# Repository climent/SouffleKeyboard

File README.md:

# Soufflé Keyboard

The Soufflé Keyboard is 6×4+1+4+1 keys column-staggered split keyboard with encoder support, based on the [Sofle](https://github.com/josefadamcik/SofleKeyboard) and re-inspired by the [Lily58](https://github.com/kata0510/Lily58) keyboards. It also takes a bit of layout ideas from the Kyria and the Ferris Sweep.

Soufflé was created by [Jesus Climent](https://https://github.com/climent/).

Key features:

*   Originally based on the Sofle V1 release layout,
    *   the two pinky columns have been lowered in the Soufflé: ~5mm for the V2, ~10mm for the V3 Sweep
    *   the thumb cluster has been repositioned to allow for equal reach of the keys
    *   a palm key has been added at the bottom of the outer pinkie column
*   Choice between rotary encoder or key switch for the inner keys.
*   Redone track layout with simplified, curved tracks.
*   V3 adds support for nice!nano with solder points for a battery and a power switch. 
*   Removed i2c communication betweek halves.

The VR release is a result of me experimenting with the RGB layout. However, I could not adapt to the displaced thumb cluster, so I returned to the V1 layout when I designed the V2.

## Images of keyboard

## Build notes

Build guide will be added soon. Meanwhile, the [Sofle Build Guide](https://josefadamcik.github.io/SofleKeyboard/build_guide.html) should be a good starting point.

## BOM

| Item                                                       | Quantity | Notes                                                                                                                                                                                                                                                |
|------------------------------------------------------------|----------|------------------------------------------------------------------------------------------------------------------------------------------------------------------------------------------------------------------------------------------------------|
| Soufflé PCB                                                | 2        |                                                                                                                                                                                                                                                      |
| Soufflé Plates                                             | 2+2      | Gerber files are provided to be ordered made of FR4. Can be 3D printed, extruding the upper plate at 1.5mm, the lower at a minimum of 1.5mm.                                                                                                         |
| Pro Micro pin MCU, or equivalent.                          | 2        | RP2040 recomended. Alternatives: Pro Micro (or clone), Elite-C, Elite-Pi, Frood, Liatris, nice!nano (for BT wireless)                                                                                                                                |
| 1N4148W Diodes                                             | 60       |                                                                                                                                                                                                                                                      |
| Kailh MX hotswap switch sockets                            | 60       |                                                                                                                                                                                                                                                      |
| MX switches                                                | 60       |                                                                                                                                                                                                                                                      |
| 1u keycaps                                                 | 60       |                                                                                                                                                                                                                                                      |
| M2, 7 mm brass (or other material) spacers                 | 10       | These are the optimal spacers. Longer ones work, too, but with 7mm the gap is minimal.                                                                                                                                                               |
| M2x0.4mm, 5mm length flat head screws                      | 20       |                                                                                                                                                                                                                                                      |
| M2x0.4mm, 7mm length flat head screws                      | 4        | If using OLED screen plexiglass protectors.                                                                                                                                                                                                          |
| PJ-320A TRRS 3.5mm Audio Jack Connector Through Holes      | 2        | Not necessary if you are using wireless, via nice!nano.                                                                                                                                                                                              |
| Surface Momentary Tact Switch, 3mm x 4mm x 4.3mm           | 2        |                                                                                                                                                                                                                                                      |
| 2.54mm Round Hole Male Tin Gold Female Pin Headers, 40p    | 2 (opt)  | HIGHLY RECOMMENDED. However, If you want to solder the MCU directly to the board, these are not necessary.                                                                                                                                           |
| Mill Max socket pins                                       | 48 (opt) | Add 8 extra for the OLED screen, if used. Alternatively, socketing can also be done with diode legs.                                                                                                                                                 |
| 1.25u keycaps                                              | 2 (opt)  | Alternative to 2x 1u keycaps.                                                                                                                                                                                                                        |
| SSD1306 128x64 OLED                                        | 2 (opt)  |                                                                                                                                                                                                                                                      |
| EC11 Encoder                                               | 2 (opt)  | Optional, as the board allows for either 2x encoders or switches.                                                                                                                                                                                    |
| Encoder knob, 16mm                                         | 2 (opt)  | If encoders are used.                                                                                                                                                                                                                                |
| M2, 10 mm brass (or other material) spacers                | 4 (opt)  | If using OLED screen plexiglass protectors.                                                                                                                                                                                                          |
| MSK12C02 power switches                                    | 2        | If using nice!nano MCUs and batteries, for BT wireless.                                                                                                                                                                                              |
| Battery, 10mAH                                             | 2        | If using nice!nano MCUs and batteries, for BT wireless.                                                                                                                                                                                              |
| TRRS audio cable, for connecting both sides                | 1 (opt)  | Not necessary if you are using BT wireless, via nice!nano.                                                                                                                                                                                           |

## Firmware 

Soufflé uses [QMK firmware](https://qmk.fm/) and it is fully compatible with the Sofle firmware.

## Default layout 

Soufflé uses a similar layout than the Sofle, with a full 6x5 matrix, and the encoders connected to the same pins. The main difference is the position of the outermost thumb key, which has been moved to the bottom of the pinky column, to be used with the palm.

## Older versions

In this repository you will find several  releases of the Soufflé Keyboard:

*   V1: Based on the Sofle v1 and the Lily58. Key features:
    *   Added the palm key at the bottom of the pinky column.
    *   Some re-routing done and some label fixes, but modtly unchanged from the Sofle v1.
*   VR: Based on the Sofle RGB. Key features:
    *   Same palm key configuration as the V1.
    *   The layout footprint is based on the RGB, and thus the thumb cluster is slightly displaced to the center (compared to the V1).
    *   The encoder footprint shares a switch footprint, allowing for the user to choose what to put there.
    *   Pins for the encoder/switch have been exposed, as the top case plate can accommodate a roller encoder.
*   V2: Based on the Soufflé V1. Key features:
    *   Same palm key configuration as the V1.
    *   Pinkie columns have been lowered.
    *   Thumb cluster repositioned, to make the keys slightly more accessible.
    *   The encoder footprint shares a switch footprint, allowing to choose what to put there.
    *   Removed I2C connectivity option.
    *   Curved contour of the keyboard.
*   V3: Based on the Soufflé V2, and the Ferris Sweep layout. Key features:
    *   Wireless compatible with Nice!Nano MCUs.
    *   Same palm key configuration as the previous releases.
    *   Pinkie columns have been lowered even further, similar to the Ferris Sweep keyboard.
    *   Middle finger column has been raised, similar to the Ferris Sweep keyboard.
    *   Thumb cluster repositioned, to make the keys slightly more accessible, as the V2.
    *   The encoder footprint shares a switch footprint, allowing to choose what to put there, as the V2.
    *   The reset button has been repositioned, and is accessible through a hole in the lower plate.
    *   Added battery connection points, and a power switch, for use with nice!nano.
    *   Removed I2C connectivity option.
    *   Curved contour of the keyboard.
*   V3.1: Small upgrade to the V3
    *   Added a compatibility pin for Nice!View screens.

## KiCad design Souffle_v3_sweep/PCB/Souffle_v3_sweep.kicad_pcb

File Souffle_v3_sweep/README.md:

# Soufflé Keyboard v3 Sweep

Soufflé v3 is 6×4+1+4+1 keys column-staggered split keyboard with encoder, OLED, palm key and nice!nano support. It is an evolution of the Soufflé V2 keyboard, with a more aggressive arrangement of the pinkie columns.

Soufflé V3 Sweep was created by [Jesus Climent](https://https://github.com/climent/).

Key changes compared to the Soufflé V2:

*   Pinkie columns have been lowered ~5mm (~10mm compared to V1), to make them more accessible.
*   Middle finger column has been raised ~3mm.
*   Reset button has been moved to an internal position, and the lower plate has a hole, making it accessible from the bottom of the keyboard.
## Firmware 

Soufflé v3 Sweep uses [QMK firmware](https://qmk.fm/) and it is fully compatible with the Sofle firmware.

## Images of keyboard

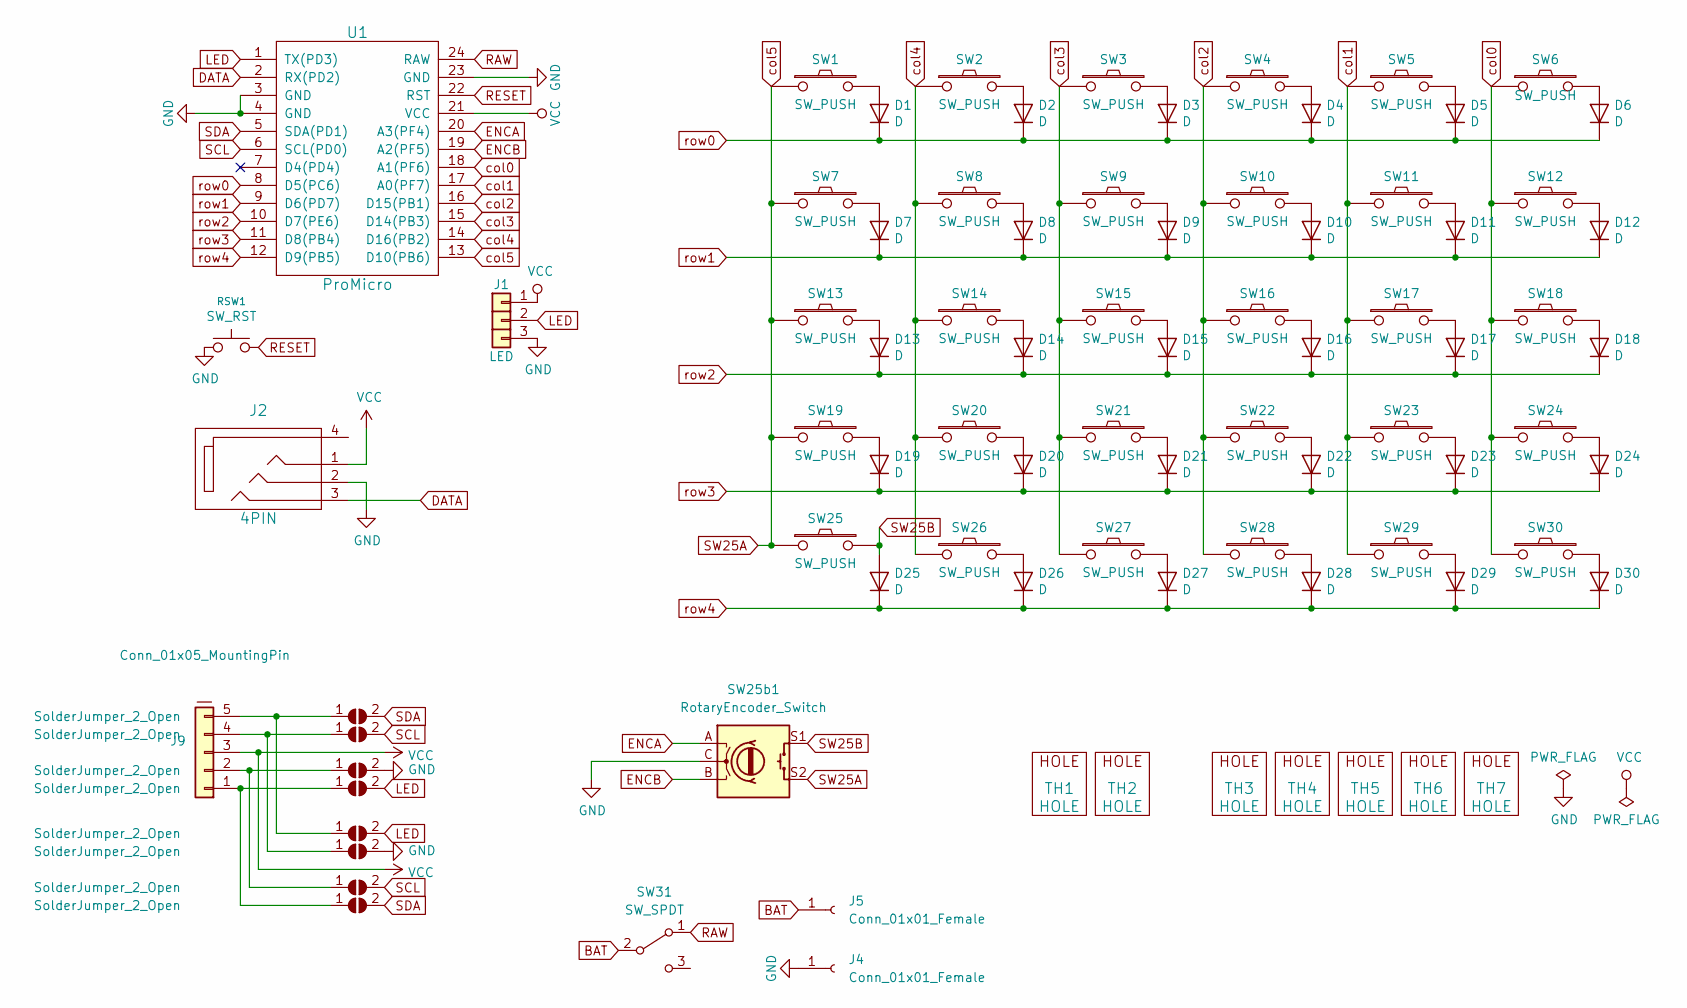
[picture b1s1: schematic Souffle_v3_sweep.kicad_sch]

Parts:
D1, D2, D3, D4, D5, D6, D7, D8, D9, D10, D11, D12, D13, D14, D15, D16, D17, D18, D19, D20, D21, D22, D23, D24, D25, D26, D27, D28, D29, D30: D; Diode_SOD123
J1: LED
J2: 4PIN; MJ-4PP-9
J4, J5: Conn_01x01_Female; PinSocket_1x01_P2.00mm_Vertical
J9: Conn_01x05_MountingPin; PinHeader_1x05_P2.54mm_Vertical
JP9, JP10, JP12, JP13, JP14, JP15, JP17, JP18: SolderJumper_2_Open; SolderJumper-2_P1.3mm_Open_Pad1.0x1.5mm
RSW1: SW_RST; TACT_SWITCH_TVBP06
SW1, SW2, SW3, SW4, SW5, SW6, SW7, SW8, SW9, SW10, SW11, SW12, SW13, SW14, SW15, SW16, SW17, SW18, SW19, SW20, SW21, SW22, SW23, SW24, SW27, SW28, SW29, SW30: SW_PUSH; CherryMX_KailhLowProfile_Hotswap
SW25, SW26: SW_PUSH; CherryMX_KailhLowProfile_Hotswap_1.5
SW25b1: RotaryEncoder_Switch; RotaryEncoder_Alps_EC11E-Switch_Vertical_H20mm
SW31: SW_SPDT; Switch_MSK-12C01-07
TH1, TH2: HOLE; M2_HOLE_PCB
TH3, TH4, TH5, TH6, TH7: HOLE; HOLE_M2_TH
U1: ProMicro

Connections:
BAT: J5.1, SW31.2 (B)
DATA: J2.3, U1.2 (RX(PD2))
ENCA: SW25b1.A, U1.20 (A3(PF4))
ENCB: SW25b1.B, U1.19 (A2(PF5))
GND: J1.3, J2.2, J4.1, JP12.2 (B), JP15.2 (B), RSW1.1, SW25b1.C, U1.3 (GND), U1.4 (GND), U1.23 (GND)
LED: J1.2, JP13.2 (B), JP14.2 (B), U1.1 (TX(PD3))
unnamed: D1.2 (A), SW1.2
unnamed: D2.2 (A), SW2.2
unnamed: D3.2 (A), SW3.2
unnamed: D4.2 (A), SW4.2
unnamed: D5.2 (A), SW5.2
unnamed: D6.2 (A), SW6.2
unnamed: D7.2 (A), SW7.2
unnamed: D8.2 (A), SW8.2
unnamed: D9.2 (A), SW9.2
unnamed: D10.2 (A), SW10.2
unnamed: D11.2 (A), SW11.2
unnamed: D12.2 (A), SW12.2
unnamed: D13.2 (A), SW13.2
unnamed: D14.2 (A), SW14.2
unnamed: D15.2 (A), SW15.2
unnamed: D16.2 (A), SW16.2
unnamed: D17.2 (A), SW17.2
unnamed: D18.2 (A), SW18.2
unnamed: D19.2 (A), SW19.2
unnamed: D20.2 (A), SW20.2
unnamed: D21.2 (A), SW21.2
unnamed: D22.2 (A), SW22.2
unnamed: D23.2 (A), SW23.2
unnamed: D24.2 (A), SW24.2
unnamed: D26.2 (A), SW26.2
unnamed: D27.2 (A), SW27.2
unnamed: D28.2 (A), SW28.2
unnamed: D29.2 (A), SW29.2
unnamed: D30.2 (A), SW30.2
unnamed: J9.1, JP13.1 (A), JP18.1 (A)
unnamed: J9.2, JP12.1 (A), JP17.1 (A)
unnamed: J9.4, JP10.1 (A), JP15.1 (A)
unnamed: J9.5, JP9.1 (A), JP14.1 (A)
RAW: SW31.1 (A), U1.24 (RAW)
RESET: RSW1.2, U1.22 (RST)
SCL: JP10.2 (B), JP17.2 (B), U1.6 (SCL(PD0))
SDA: JP9.2 (B), JP18.2 (B), U1.5 (SDA(PD1))
SW25A: SW1.1, SW7.1, SW13.1, SW19.1, SW25.1, SW25b1.S2, U1.13 (D10(PB6))
SW25B: D25.2 (A), SW25.2, SW25b1.S1
VCC: J1.1, J2.1, J9.3, U1.21 (VCC)
col0: SW6.1, SW12.1, SW18.1, SW24.1, SW30.1, U1.18 (A1(PF6))
col1: SW5.1, SW11.1, SW17.1, SW23.1, SW29.1, U1.17 (A0(PF7))
col2: SW4.1, SW10.1, SW16.1, SW22.1, SW28.1, U1.16 (D15(PB1))
col3: SW3.1, SW9.1, SW15.1, SW21.1, SW27.1, U1.15 (D14(PB3))
col4: SW2.1, SW8.1, SW14.1, SW20.1, SW26.1, U1.14 (D16(PB2))
row0: D1.1 (K), D2.1 (K), D3.1 (K), D4.1 (K), D5.1 (K), D6.1 (K), U1.8 (D5(PC6))
row1: D7.1 (K), D8.1 (K), D9.1 (K), D10.1 (K), D11.1 (K), D12.1 (K), U1.9 (D6(PD7))
row2: D13.1 (K), D14.1 (K), D15.1 (K), D16.1 (K), D17.1 (K), D18.1 (K), U1.10 (D7(PE6))
row3: D19.1 (K), D20.1 (K), D21.1 (K), D22.1 (K), D23.1 (K), D24.1 (K), U1.11 (D8(PB4))
row4: D25.1 (K), D26.1 (K), D27.1 (K), D28.1 (K), D29.1 (K), D30.1 (K), U1.12 (D9(PB5))

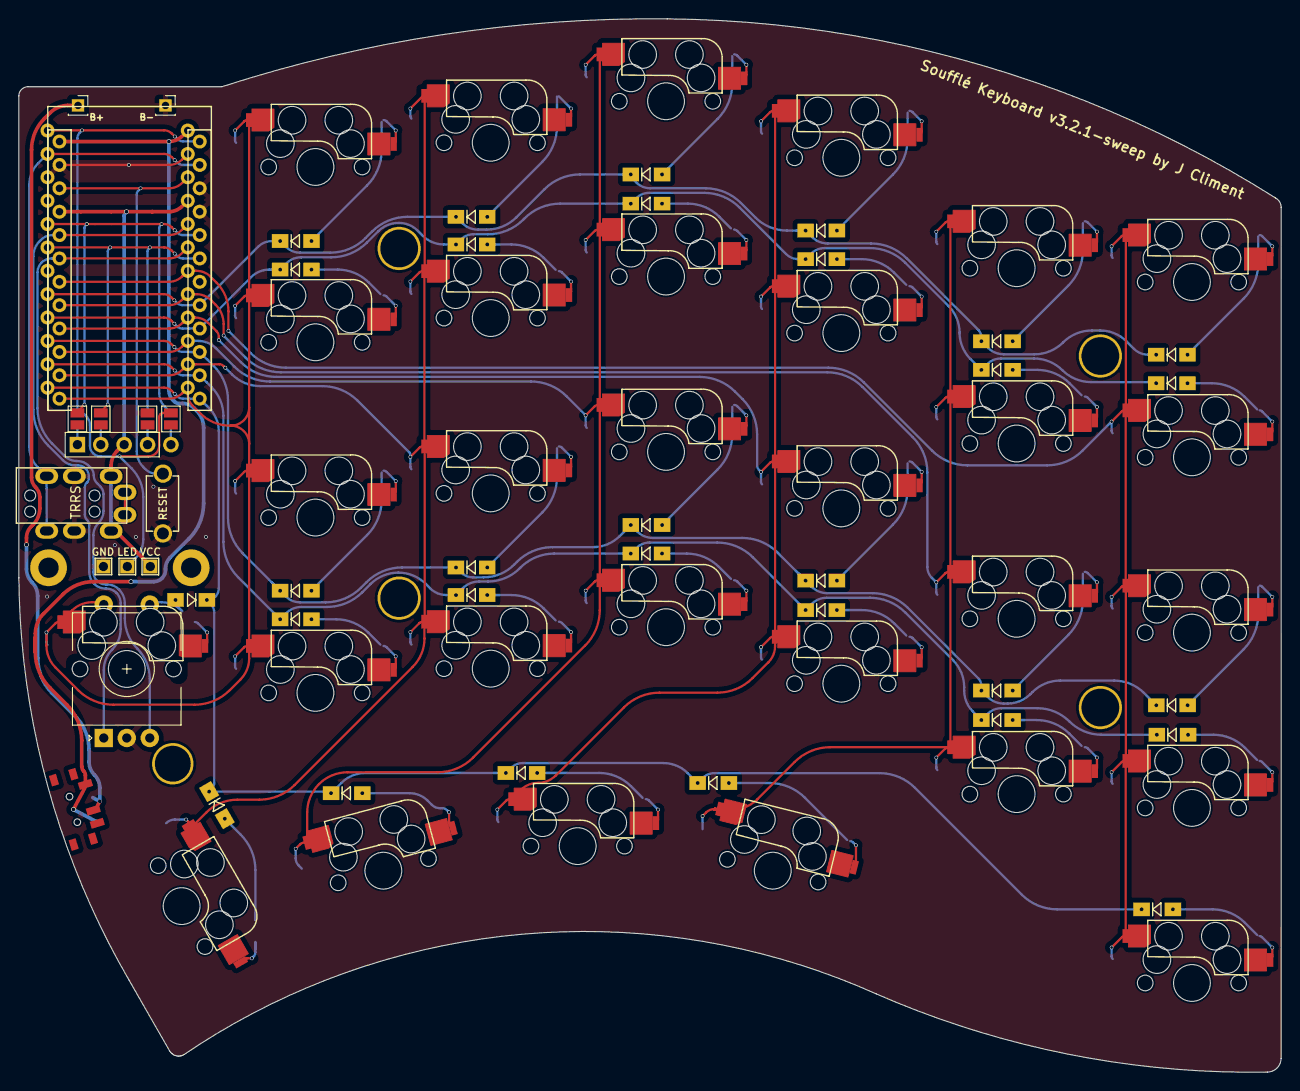
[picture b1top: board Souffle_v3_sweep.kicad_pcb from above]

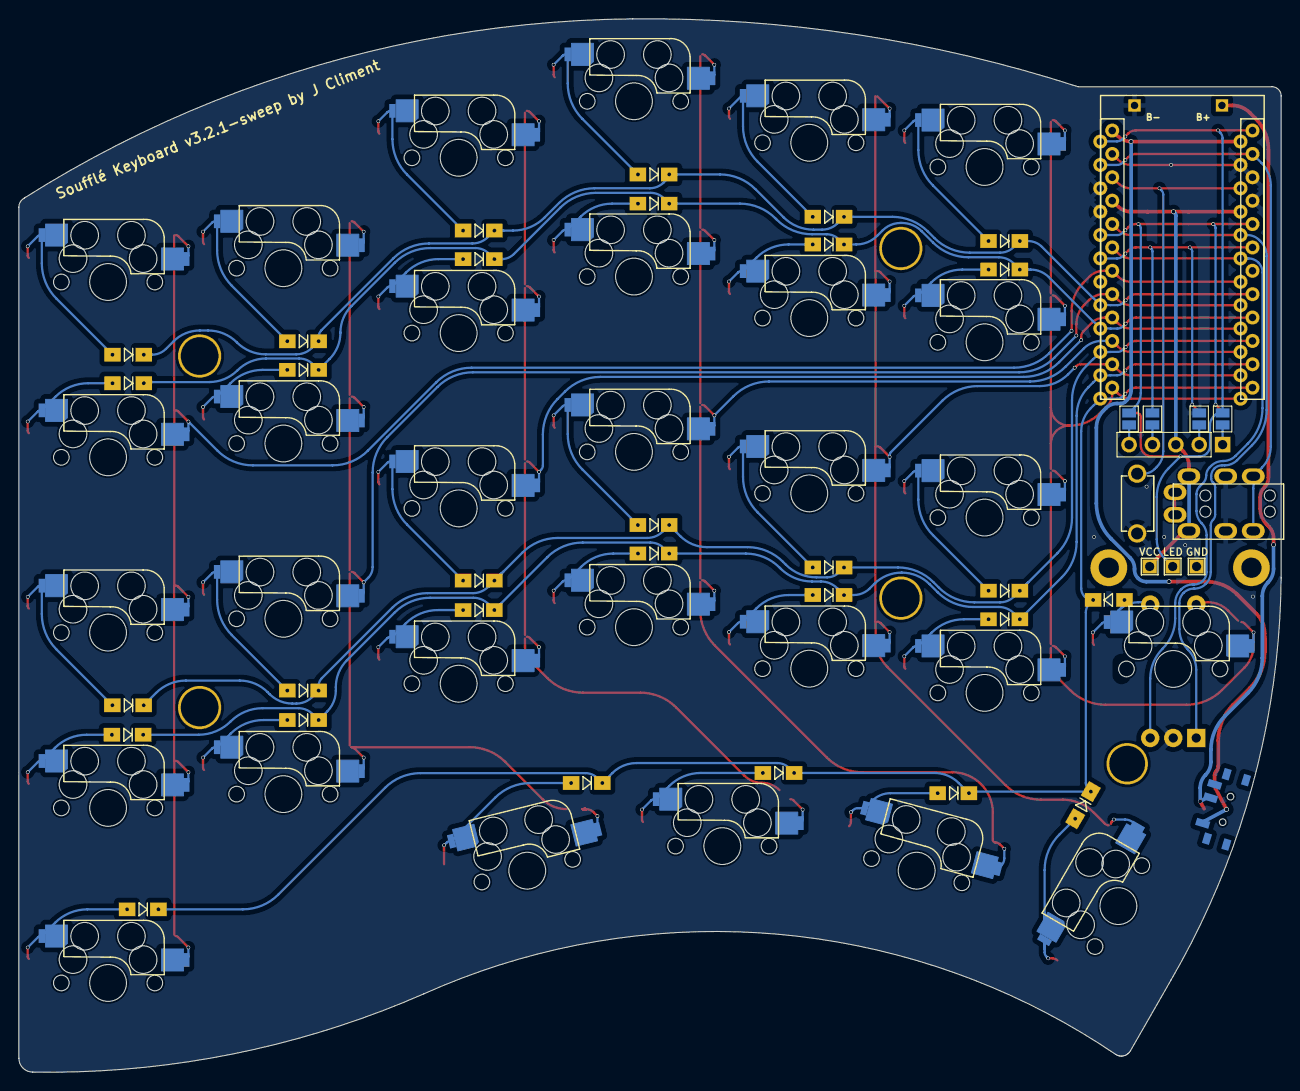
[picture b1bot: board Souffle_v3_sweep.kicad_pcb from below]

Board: 2 copper layers, 137.2 x 114.5 mm, 84 parts (4 on the bottom side), 56 nets.

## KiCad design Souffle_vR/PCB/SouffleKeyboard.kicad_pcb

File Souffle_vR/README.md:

# Soufflé Keyboard

Soufflé vR is 6×4+1+4+1 keys column-staggered split keyboard with encoder support, based on the [Sofle](https://github.com/josefadamcik/SofleKeyboard) RGB version, and re-inspired by the [Lily58](https://github.com/kata0510/Lily58) keyboard.

Soufflé was created by [Jesus Climent](https://https://github.com/climent/).

Key features:

*   Palm key at the bottom of the outer pinky column.
*   2x rotary encoders.
*   Original RGB features were removed.
*   Exposed pins for roller encoder on the upper case plate. 
*   More (to be listed).

## Firmware 

Soufflé uses [QMK firmware](https://qmk.fm/) and it is fully compatible with the Sofle firmware.

## Default layout 

Soufflé uses a similar layout than the Sofle, with a full 6x5 matrix, and the encoders connected to the same pins. The main difference is the position of the outermost thumb key, which has been moved to the bottom of the pinky column, to be used with the palm.

## Images of keyboard

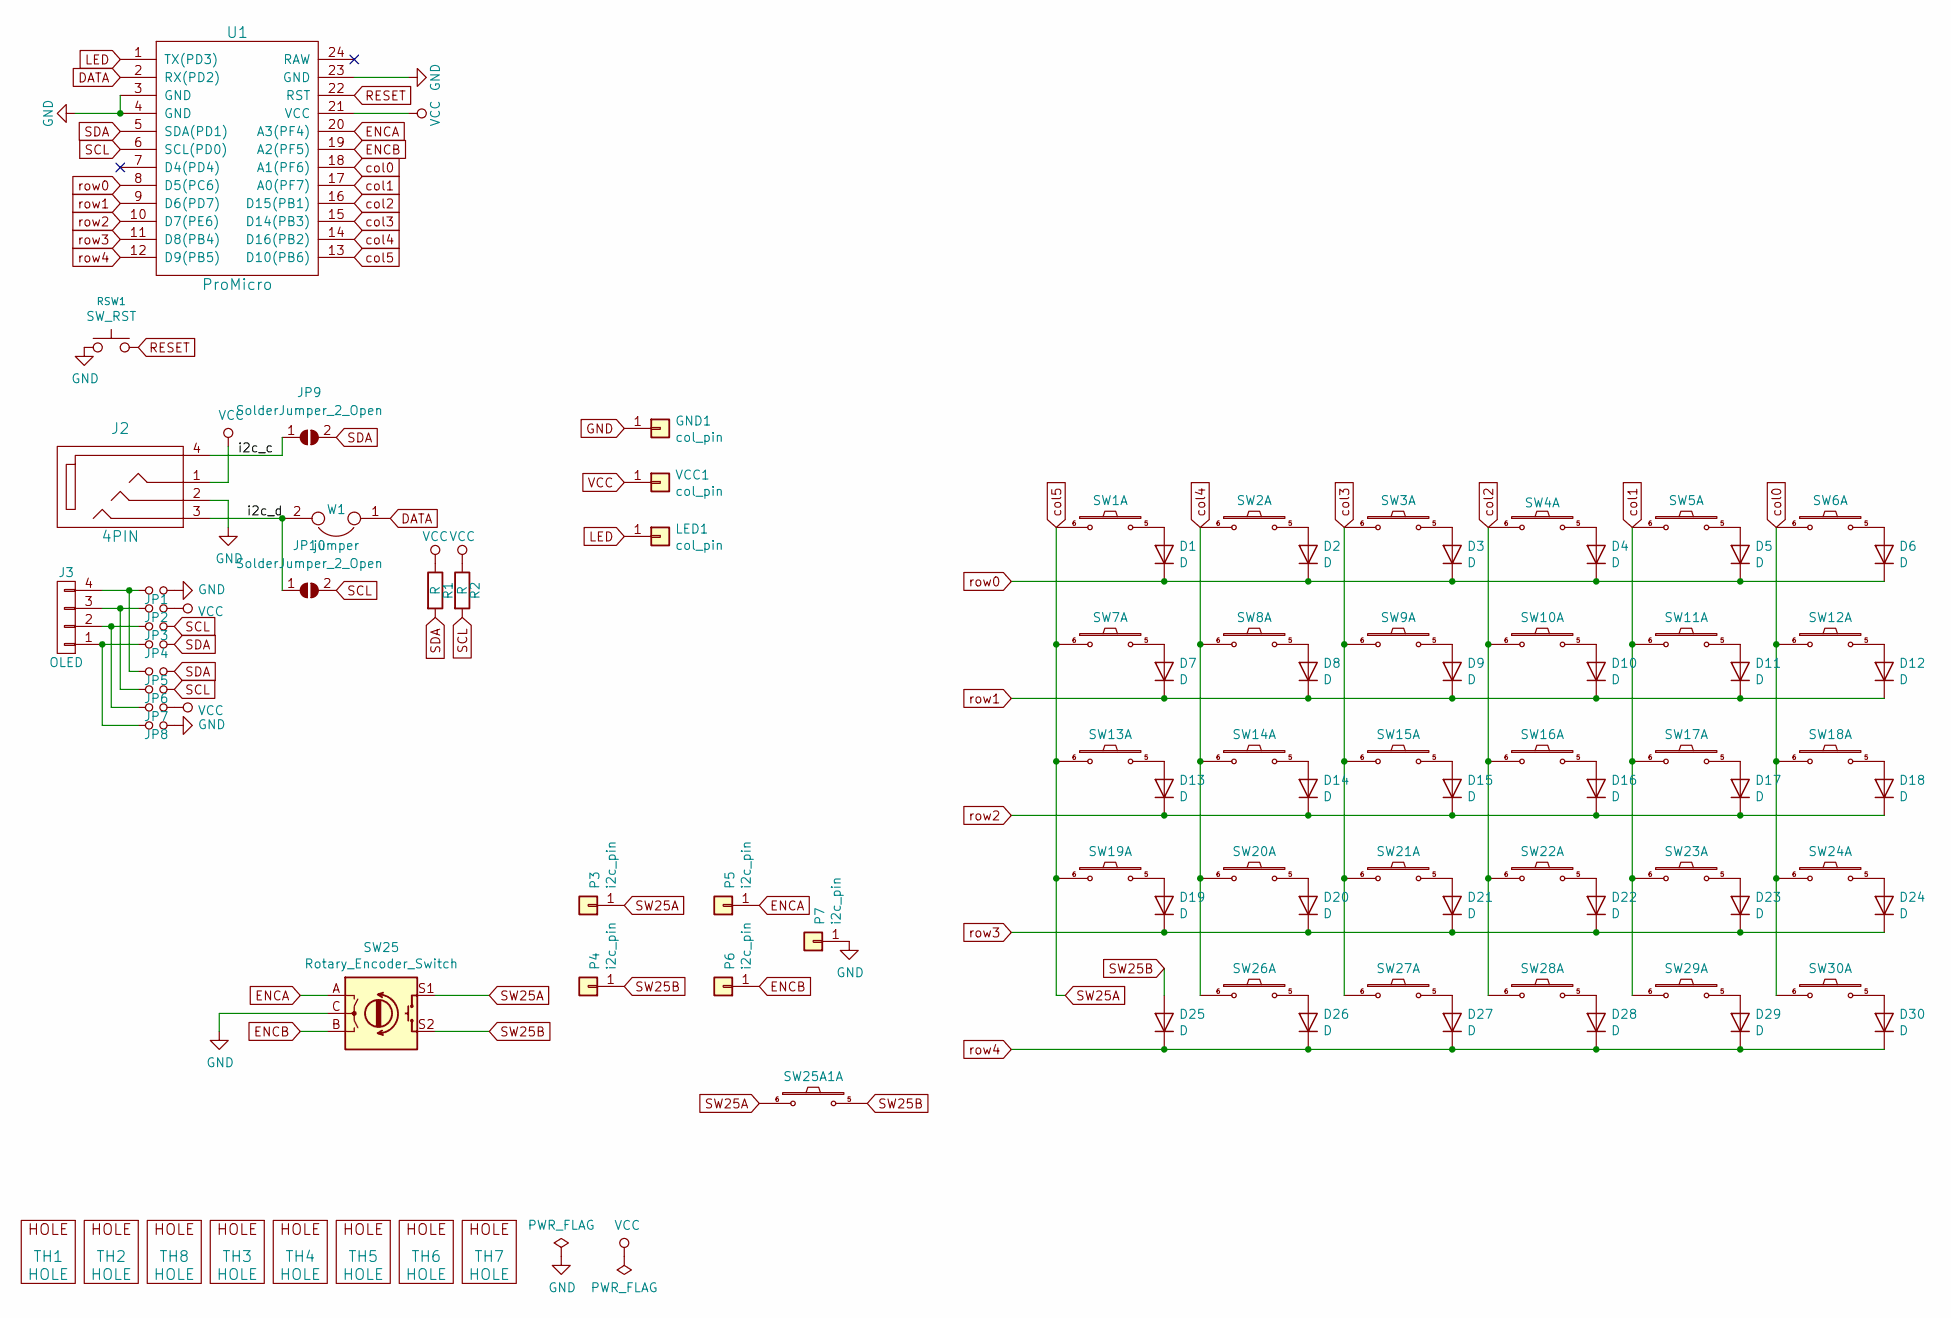
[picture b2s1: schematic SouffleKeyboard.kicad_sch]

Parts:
D1, D2, D3, D4, D5, D6, D7, D8, D9, D10, D11, D12, D13, D14, D15, D16, D17, D18, D19, D20, D21, D22, D23, D24, D25, D26, D27, D28, D29, D30: D; crkbd-diode
GND1: col_pin; 1pin_conn
J2: 4PIN; MJ-4PP-9
J3: OLED; OLED_4Pin
JP1, JP2, JP3, JP4, JP5, JP6, JP7, JP8: Jumper_NO_Small; Jumper
JP9, JP10: SolderJumper_2_Open; Jumper
LED1: col_pin; 1pin_conn
P3, P4, P5, P6, P7: i2c_pin; 1pin_conn
R1, R2: R; RESISTOR_mini
RSW1: SW_RST; TACT_SWITCH_TVBP06
SW1, SW2, SW3, SW4, SW5, SW6, SW7, SW8, SW9, SW10, SW11, SW12, SW13, SW14, SW15, SW16, SW17, SW18, SW19, SW20, SW21, SW22, SW23, SW24, SW25A1, SW26, SW27, SW28, SW29, SW30: SW_PUSH-MX_W_LED; SK6812MINI_and_cherry_NoLEDPads
SW25: Rotary_Encoder_Switch; RotaryEncoder_Alps_EC11E-Switch_Vertical_H20mm-keebio_modif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
TH1, TH2, TH8: HOLE; M2_HOLE_PCB
TH3, TH4, TH5, TH6, TH7: HOLE; HOLE_M2_TH
U1: ProMicro
VCC1: col_pin; 1pin_conn
W1: jumper; jumper_data

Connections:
/i2c_c: J2.4, JP9.1 (A)
/i2c_d: J2.3, JP10.1 (A), W1.2
DATA: U1.2 (RX(PD2)), W1.1
ENCA: P5.1, SW25.A, U1.20 (A3(PF4))
ENCB: P6.1, SW25.B, U1.19 (A2(PF5))
GND: GND1.1, J2.2, JP1.2, JP8.2, P7.1, RSW1.1, SW25.C, U1.3 (GND), U1.4 (GND), U1.23 (GND)
LED: LED1.1, U1.1 (TX(PD3))
unnamed: D1.2 (A), SW1.5
unnamed: D2.2 (A), SW2.5
unnamed: D3.2 (A), SW3.5
unnamed: D4.2 (A), SW4.5
unnamed: D5.2 (A), SW5.5
unnamed: D6.2 (A), SW6.5
unnamed: D7.2 (A), SW7.5
unnamed: D8.2 (A), SW8.5
unnamed: D9.2 (A), SW9.5
unnamed: D10.2 (A), SW10.5
unnamed: D11.2 (A), SW11.5
unnamed: D12.2 (A), SW12.5
unnamed: D13.2 (A), SW13.5
unnamed: D14.2 (A), SW14.5
unnamed: D15.2 (A), SW15.5
unnamed: D16.2 (A), SW16.5
unnamed: D17.2 (A), SW17.5
unnamed: D18.2 (A), SW18.5
unnamed: D19.2 (A), SW19.5
unnamed: D20.2 (A), SW20.5
unnamed: D21.2 (A), SW21.5
unnamed: D22.2 (A), SW22.5
unnamed: D23.2 (A), SW23.5
unnamed: D24.2 (A), SW24.5
unnamed: D26.2 (A), SW26.5
unnamed: D27.2 (A), SW27.5
unnamed: D28.2 (A), SW28.5
unnamed: D29.2 (A), SW29.5
unnamed: D30.2 (A), SW30.5
unnamed: J3.1, JP4.1, JP8.1
unnamed: J3.2, JP3.1, JP7.1
unnamed: J3.3, JP2.1, JP6.1
unnamed: J3.4, JP1.1, JP5.1
RESET: RSW1.2, U1.22 (RST)
SCL: JP3.2, JP6.2, JP10.2 (B), R2.2, U1.6 (SCL(PD0))
SDA: JP4.2, JP5.2, JP9.2 (B), R1.2, U1.5 (SDA(PD1))
SW25A: P3.1, SW1.6, SW7.6, SW13.6, SW19.6, SW25.S1, SW25A1.6, U1.13 (D10(PB6))
SW25B: D25.2 (A), P4.1, SW25.S2, SW25A1.5
VCC: J2.1, JP2.2, JP7.2, R1.1, R2.1, U1.21 (VCC), VCC1.1
col0: SW6.6, SW12.6, SW18.6, SW24.6, SW30.6, U1.18 (A1(PF6))
col1: SW5.6, SW11.6, SW17.6, SW23.6, SW29.6, U1.17 (A0(PF7))
col2: SW4.6, SW10.6, SW16.6, SW22.6, SW28.6, U1.16 (D15(PB1))
col3: SW3.6, SW9.6, SW15.6, SW21.6, SW27.6, U1.15 (D14(PB3))
col4: SW2.6, SW8.6, SW14.6, SW20.6, SW26.6, U1.14 (D16(PB2))
row0: D1.1 (K), D2.1 (K), D3.1 (K), D4.1 (K), D5.1 (K), D6.1 (K), U1.8 (D5(PC6))
row1: D7.1 (K), D8.1 (K), D9.1 (K), D10.1 (K), D11.1 (K), D12.1 (K), U1.9 (D6(PD7))
row2: D13.1 (K), D14.1 (K), D15.1 (K), D16.1 (K), D17.1 (K), D18.1 (K), U1.10 (D7(PE6))
row3: D19.1 (K), D20.1 (K), D21.1 (K), D22.1 (K), D23.1 (K), D24.1 (K), U1.11 (D8(PB4))
row4: D25.1 (K), D26.1 (K), D27.1 (K), D28.1 (K), D29.1 (K), D30.1 (K), U1.12 (D9(PB5))

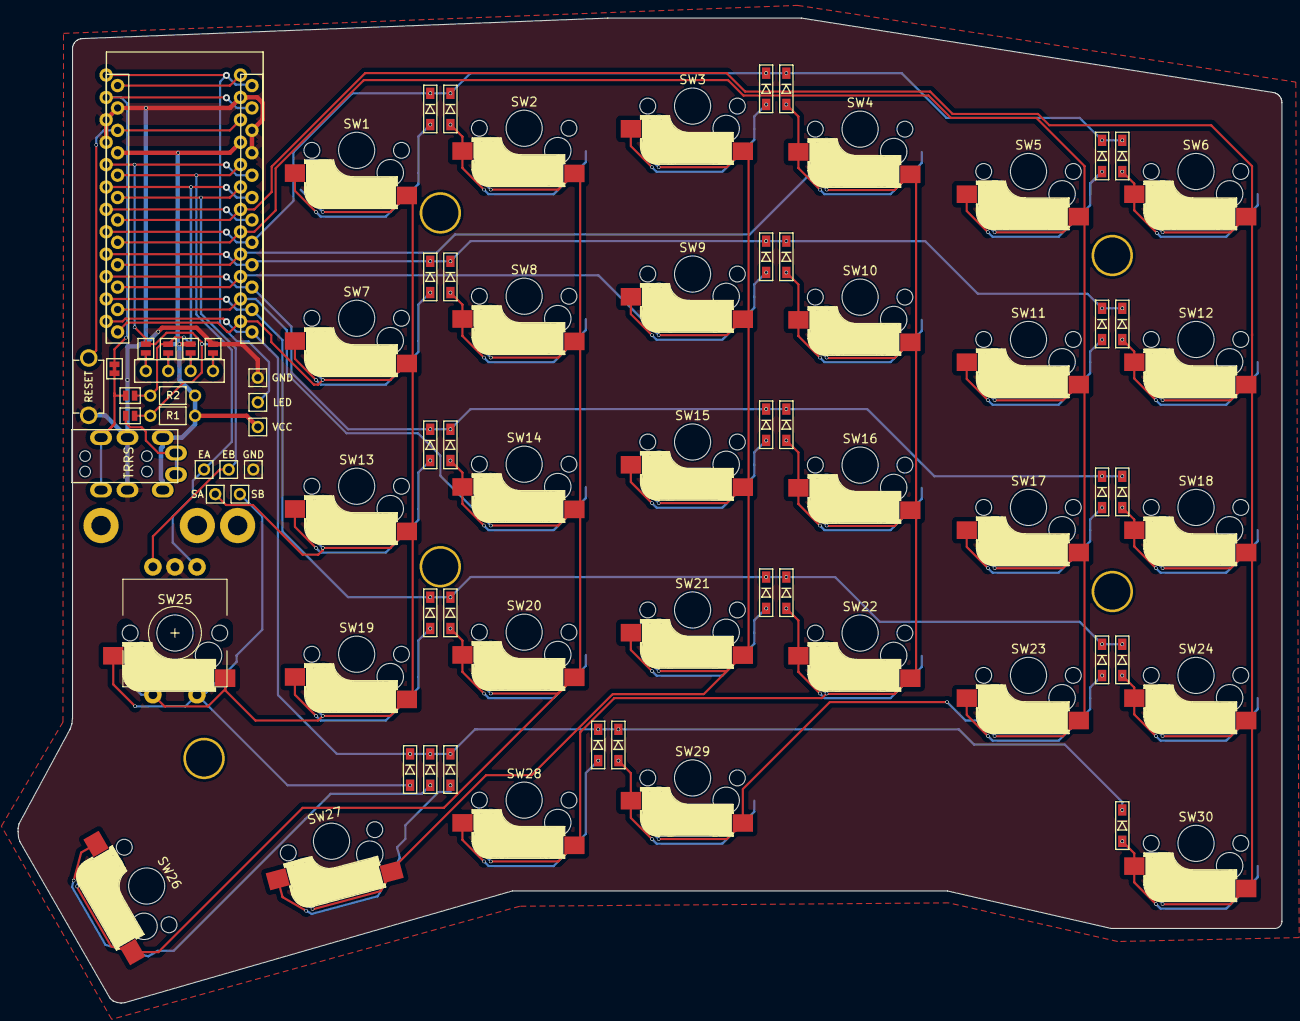
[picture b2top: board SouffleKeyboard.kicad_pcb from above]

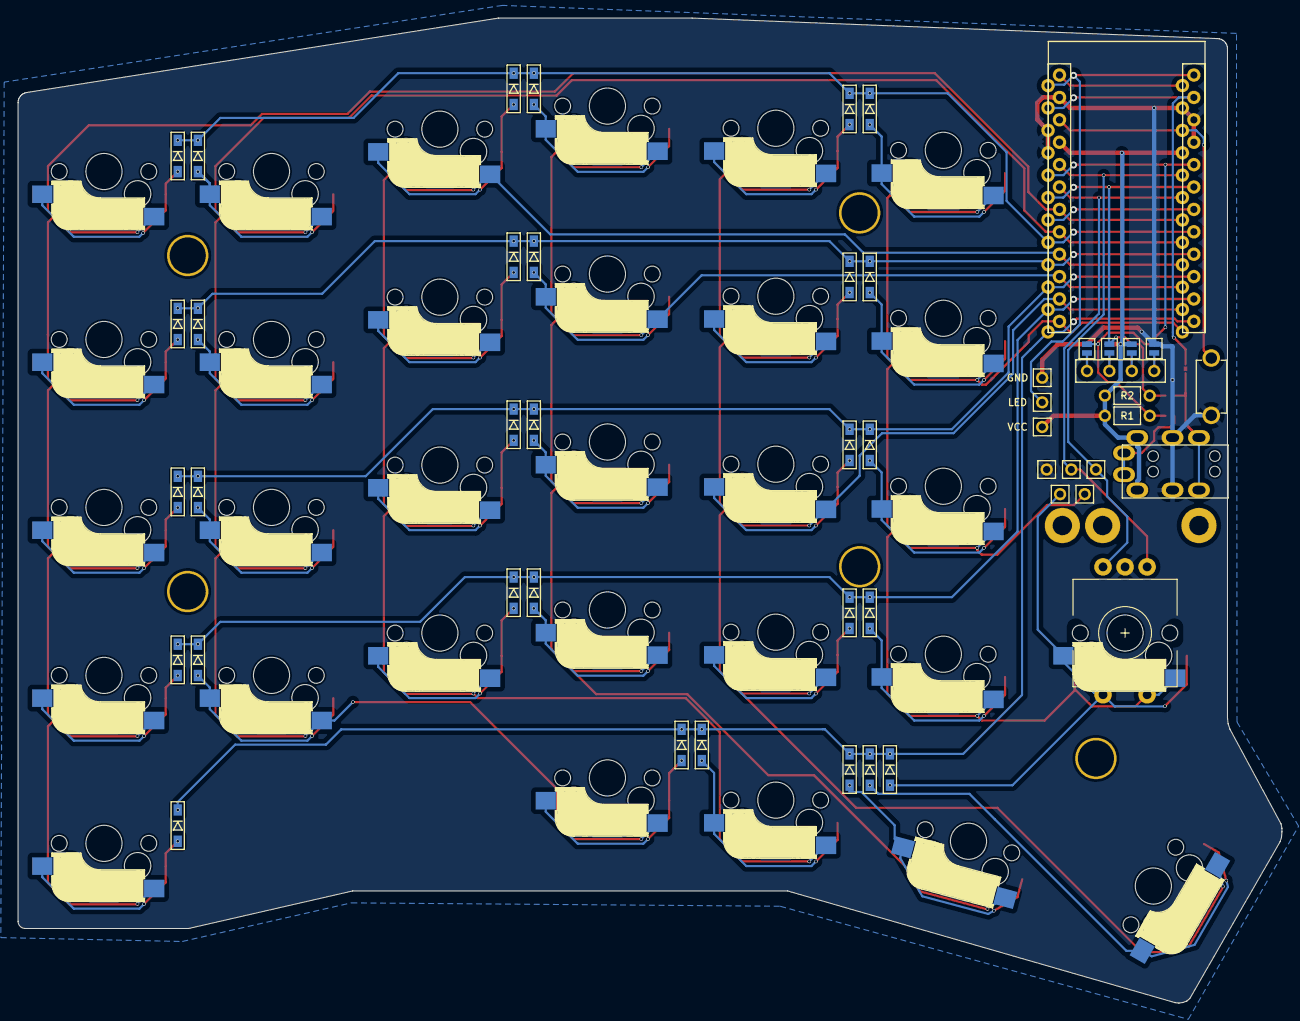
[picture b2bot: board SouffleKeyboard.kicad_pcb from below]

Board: 2 copper layers, 143.3 x 111.7 mm, 94 parts (4 on the bottom side), 56 nets.

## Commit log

2022-07-24 Initial release of the Soufflé v2.
2022-07-24 Added gerbers, updated README.
2022-07-25 Added new images, backup files updated.
2022-07-31 Rotated reset key for shorter track.
2022-07-31 Fix track for column 2. Was unconnected.
2022-07-31 Exported gerber files for fixed v2.
2022-07-31 Deleted backup file.
2022-07-31 Souffle v1.
2022-07-31 Souffle vR (modeled after the Sofle RGB)..
2022-07-31 Updated README and small changed on layout.
2022-08-01 Added images of previous releases.
2022-08-01 Added README.md for v1.
2022-08-01 Added README.md for vR.
2022-08-01 Added case plate with roller encoder.
2022-08-01 Added case with partial drilling of holes.
2022-08-01 Small tweaks.
2022-08-25 Small fix for 2u keys in the thumb cluster touching the OLED key.
2023-02-11 Initial underglow changes.
2023-02-11 Checkpoint commit.
2023-02-12 LED placement and VCC pad for electricity supply to LEDs.
2023-03-03 Backup
2023-03-04 Initial release of V3 with sweep key layout.
2023-03-04 Added gitignore file.
2023-03-04 More underglow changes.
2023-03-04 Updated case plates, updated pcb.
2023-03-04 Removed circle.
2023-03-05 Added battery pins and power switch for nice!nano option.
2023-03-11 Updated plot options.
2023-03-11 Added .gitignore to branch.
2023-03-11 Small track changes.
2023-03-11 Updated gerber options.
2023-03-12 Adjusted an edge reported by JLCPCB as too thin.
2023-03-20 Added mac .DS_Store to gitignore
2023-03-20 Small updates.
2023-04-01 Soufflé v3 Sweep keyboard.
2023-04-01 Gerber files doe v3.
2023-04-02 Updated README with BOM.
2023-04-02 New v3 image.
2023-04-02 Added image.
2023-04-02 Fix typo.
2023-04-02 Added images and README for the V3 keyboard.
2023-04-02 Small fixes.
2023-04-02 Moved references and images of V2 to the actual VR
2023-04-02 Added built images of the V2.
2023-04-02 Added a README for the V2 keyboard.
2023-04-03 Updated README files.
2023-04-03 Updated BOM.
2023-04-03 Updated changelog.
2023-04-08 Specify 'W' SMD variant
2023-04-14 New footprints for Soufflé.
2023-04-14 Initial choc Soufflé.
2023-04-14 Updated choc Soufflé.
2023-04-15 Updated TH with reduced size.
2023-04-15 Build guide shamelessly forklifted from the Sofle build guide.
2023-04-15 Build guide.
2023-04-15 Build guide
2023-04-15 Fixed some small errors.
2023-04-16 Initial routing.
2023-04-16 Final Soufflé Choc PCB.
2023-04-16 New render of the V3 choc.
2023-04-16 Case plates for the V3 Choc release.
2023-04-16 Fixed horizontal spacing of the FN key.
2023-04-16 Final verifications and route cleaning.
2023-04-17 Fixed encoder center circle.
2023-04-18 Updated gitignore
2023-04-18 Fixed error in GND not connected on the right side of the OLED pads, and other small cleanups.
2023-04-19 Fixed small bug, completed comment layer.
2023-04-19 Release Choc version by merging Souffle_v3_sweep_choc branch to main repo with all the fixes.
2023-04-19 Push reset button away from the TRRS conenctor.
2023-04-20 Small changes to make sure the components do not touch each other or the board.
2023-04-20 Gerber files for the Choc v3 board.
2023-04-23 Gerber file for the corrected PCB.
2023-04-23 Corrected PCB with displaced encoder.
2023-04-26 Added steps for soldering pins and micro.
2023-05-27 Small updates on the VR release.
2023-05-27 Added gerbers for vR.
2023-05-27 Removed gerber leftover files.
2023-05-27 Updated to KiCad 7
2023-06-01 Modified gitignore.
2023-11-09 Updated text in the README.
2023-11-11 Updated PCB image in README.
2024-01-04 Added images
2024-01-04 Updated OLED connection to accomodate for NiceView option.
2024-01-04 Corrected step 5 in the build doc.
2024-01-06 Updated 3.1 release.
2024-01-06 Added Gerber file for 3.1.
2024-02-24 V3.2 of the Soufflé keyboard, with reworked NiceView pins
2024-02-24 Added license file.
2024-02-26 Updated and fixed v3.2 as the order of the pads was incorrect. Release v3.2.1 with the fix.
